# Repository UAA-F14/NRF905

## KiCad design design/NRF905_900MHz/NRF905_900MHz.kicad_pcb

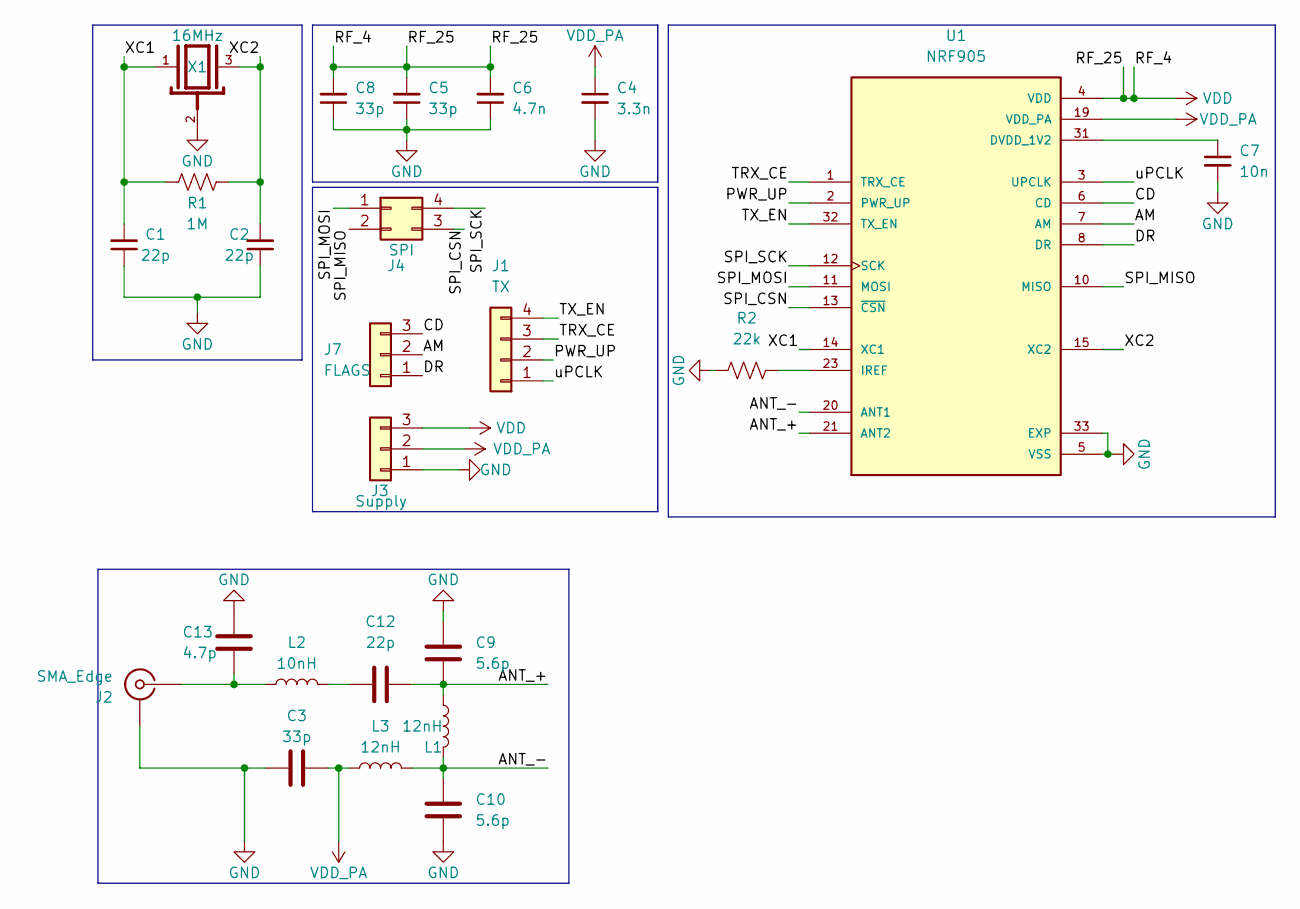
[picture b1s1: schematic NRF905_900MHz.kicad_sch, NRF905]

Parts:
C1, C2, C12: 22p; C_0603_1608Metric
C3, C5, C8: 33p; C_0603_1608Metric
C4: 3.3n; C_0603_1608Metric
C6: 4.7n; C_0603_1608Metric
C7: 10n; C_0603_1608Metric
C9, C10: 5.6p; C_0603_1608Metric
C13: 4.7p; C_0603_1608Metric
J1: TX; PinSocket_1x04_P2.54mm_Vertical
J2: SMA_Edge; SMA_Amphenol_132291-12_Vertical
J3: Supply; PinHeader_1x03_P2.54mm_Vertical
J4: SPI
J7: FLAGS; PinHeader_1x03_P2.54mm_Vertical
L1, L3: 12nH; L_0603_1608Metric
L2: 10nH; L_0603_1608Metric
R1: 1M; R_0603_1608Metric
R2: 22k; R_0603_1608Metric
U1: NRF905; QFN-32-1EP_5x5mm_P0.5mm_EP3.1x3.1mm; MPN NRF905
X1: 16MHz; XTAL_ABM3B-16.000MHZ-10-1-U-T; MPN X322516MLB4SI

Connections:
/AM: J7.2, U1.7 (AM)
/ANT_+: C9.2, C12.2, L1.1, U1.21 (ANT2)
/ANT_-: C10.1, L1.2, L3.2, U1.20 (ANT1)
/CD: J7.3, U1.6 (CD)
/DR: J7.1, U1.8 (DR)
/PWR_UP: J1.2, U1.2 (PWR_UP)
/SPI_CSN: J4.3, U1.13 (~CSN); also elsewhere on the board
/SPI_MISO: J4.2, U1.10 (MISO); also elsewhere on the board
/SPI_MOSI: J4.1, U1.11 (MOSI); also elsewhere on the board
/SPI_SCK: J4.4, U1.12 (SCK); also elsewhere on the board
/TRX_CE: J1.3, U1.1 (TRX_CE)
/TX_EN: J1.4, U1.32 (TX_EN)
/XC1: C1.2, R1.2, U1.14 (XC1), X1.1
/XC2: C2.2, R1.1, U1.15 (XC2), X1.3
/uPCLK: J1.1, U1.3 (UPCLK)
GND: C1.1, C2.1, C3.1, C4.2, C5.1, C6.1, C7.2, C8.1, C9.1, C10.2, C13.2, J2.2 (Ext), J3.1, R2.2, U1.5 (VSS), U1.9 (VSS), U1.16 (VSS), U1.18 (VSS), U1.22 (VSS), U1.24 (VSS), U1.26 (VSS), U1.27 (VSS), U1.28 (VSS), U1.29 (VSS), U1.30 (VSS), U1.33 (EXP), X1.2, X1.4
unnamed: C12.1, L2.2
unnamed: C13.1, J2.1 (In), L2.1
unnamed: C7.1, U1.31 (DVDD_1V2)
unnamed: R2.1, U1.23 (IREF)
VDD: C5.2, C6.2, C8.2, J3.3, U1.4 (VDD), U1.17 (VDD), U1.25 (VDD)
VDD_PA: C3.2, C4.1, J3.2, L3.1, U1.19 (VDD_PA)

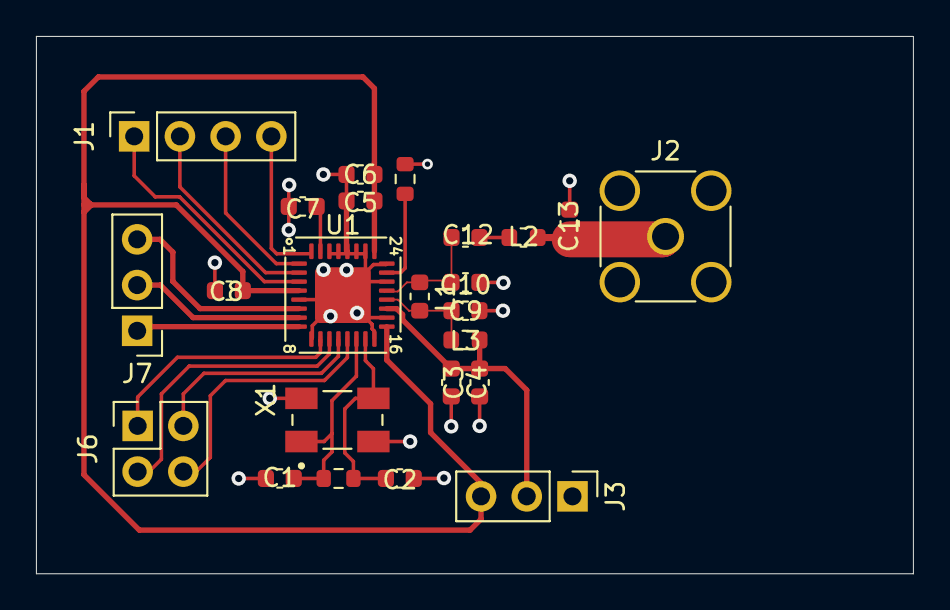
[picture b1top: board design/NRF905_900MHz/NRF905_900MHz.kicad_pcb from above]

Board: 2 copper layers, 48.7 x 29.9 mm, 24 parts (0 on the bottom side), 22 nets.

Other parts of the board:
J6: SPI; PinSocket_2x02_P2.54mm_Vertical

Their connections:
/SPI_CSN: J6.4; also elsewhere on the board
/SPI_MISO: J6.1; also elsewhere on the board
/SPI_MOSI: J6.2; also elsewhere on the board
/SPI_SCK: J6.3; also elsewhere on the board

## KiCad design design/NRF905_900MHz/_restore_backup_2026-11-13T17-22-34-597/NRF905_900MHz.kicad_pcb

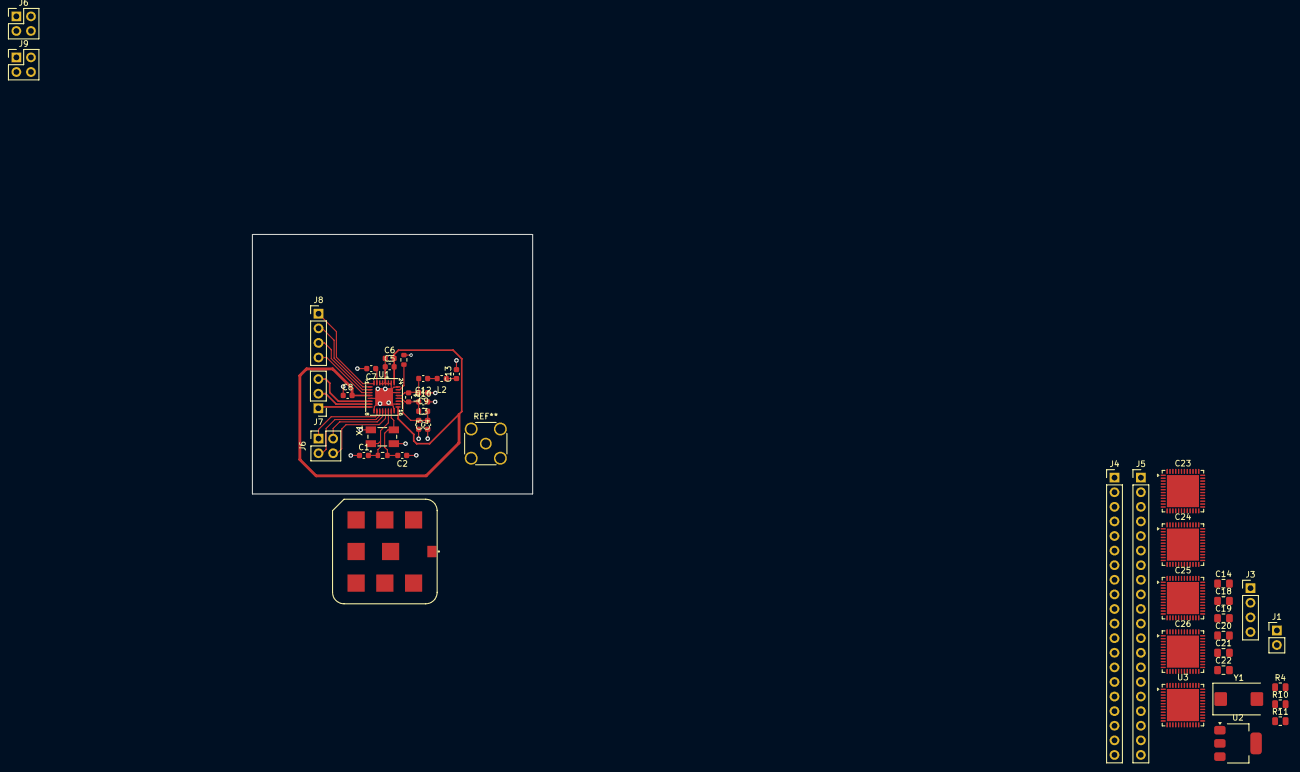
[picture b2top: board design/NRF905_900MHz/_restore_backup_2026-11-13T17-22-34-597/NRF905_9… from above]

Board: 2 copper layers, 48.8 x 45.2 mm, 45 parts (0 on the bottom side), 61 nets.

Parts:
AE1: 50 Ohm; GNSS_Ceramic_Antenna_18.0x18.0mm
C1, C2, C12: 22p; C_0603_1608Metric
C3, C5, C8: 33p; C_0603_1608Metric
C4: 3.3n; C_0603_1608Metric
C6: 4.7n; C_0603_1608Metric
C7: 10n; C_0603_1608Metric
C9, C10: 5.6p; C_0603_1608Metric
C13: 4.7p; C_0603_1608Metric
C14: 4.7uF; C_0805_2012Metric_Pad1.18x1.45mm_HandSolder
C18: 100nF; C_0805_2012Metric_Pad1.18x1.45mm_HandSolder
C19, C20: 22pF; C_0805_2012Metric_Pad1.18x1.45mm_HandSolder
C21: 10uF; C_0805_2012Metric_Pad1.18x1.45mm_HandSolder
C22: 22uF; C_0805_2012Metric_Pad1.18x1.45mm_HandSolder
C23: 1uF; QFN-48-1EP_7x7mm_P0.5mm_EP5.6x5.6mm
C24, C25, C26: 100nF; QFN-48-1EP_7x7mm_P0.5mm_EP5.6x5.6mm
J1: V_Battery; PinHeader_1x02_P2.54mm_Vertical
J3: STLINK; PinHeader_1x04_P2.54mm_Vertical
J4: BlackPill; PinHeader_1x20_P2.54mm_Vertical
J5: Conn_01x20_Socket; PinHeader_1x20_P2.54mm_Vertical
J6: SPI; PinSocket_2x02_P2.54mm_Vertical
J6#2: SPI; PinHeader_2x02_P2.54mm_Vertical
J7: FLAGS; PinHeader_1x03_P2.54mm_Vertical
J8: SPI; PinHeader_1x04_P2.54mm_Vertical
J9: TX; PinHeader_2x02_P2.54mm_Vertical
L1, L3: 12nH; L_0603_1608Metric
L2: 10nH; L_0603_1608Metric
R1: 1M; R_0603_1608Metric
R2: 22k; R_0603_1608Metric
R4, R10, R11: 10k; R_0805_2012Metric
U1: NRF905; QFN-32-1EP_5x5mm_P0.5mm_EP3.1x3.1mm
U2: AMS1117-3.3; SOT-223-3_TabPin2
U3: STM32F411CEUx; QFN-48-1EP_7x7mm_P0.5mm_EP5.6x5.6mm
X1: 16MHz; XTAL_ABM3B-16.000MHZ-10-1-U-T
Y1: 8MHz; Crystal_SMD_EuroQuartz_MQ2-2Pin_7.0x5.0mm

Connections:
3.3V: J4.18, J5.20
5V: J4.20, J5.18
/AM: J7.2, U1.7 (AM)
/ANT_+: C9.2, C12.2, L1.1, U1.21 (ANT2)
/ANT_-: C10.1, L1.2, L3.2, U1.20 (ANT1)
/CD: J7.3, U1.6 (CD)
/DR: J7.1, U1.8 (DR)
/PWR_UP: J8.3, U1.2 (PWR_UP)
/SPI_CSN: J6.4, U1.13 (~CSN)
/SPI_MISO: J6.1, U1.10 (MISO)
/SPI_MOSI: J6.2, U1.11 (MOSI)
/SPI_SCK: J6.3, U1.12 (SCK)
/TRX_CE: J8.2, U1.1 (TRX_CE)
/TX_EN: J8.1, U1.32 (TX_EN)
/XC1: C1.2, R1.2, U1.14 (XC1), X1.1
/XC2: C2.2, R1.1, U1.15 (XC2), X1.3
/uPCLK: J8.4, U1.3 (UPCLK)
A0: J4.6, U3.10 (PA0)
A1: J4.7, U3.11 (PA1)
A2: J4.8, U3.12 (PA2)
A3: J4.9, U3.13 (PA3)
A4: J4.10, U3.14 (PA4)
A5: J4.11, U3.15 (PA5)
A6: J4.12, U3.16 (PA6)
A7: J4.13, U3.17 (PA7)
A8: J5.5, U3.29 (PA8)
A9: J5.6, U3.30 (PA9)
A10: J5.7, U3.31 (PA10)
A11: J5.8, U3.32 (PA11)
A12: J5.9, U3.33 (PA12)
A15: J5.10, U3.38 (PA15)
B0: J4.14, U3.18 (PB0)
B1: J4.15, U3.19 (PB1)
B3: J5.11, U3.39 (PB3)
B4: J5.12, U3.40 (PB4)
B5: J5.13, U3.41 (PB5)
B6: J5.14, U3.42 (PB6)
B7: J5.15, U3.43 (PB7)
B8: J5.16, U3.45 (PB8)
B10: J4.17, U3.21 (PB10)
B12: J5.1, U3.25 (PB12)
B13: J5.2, U3.26 (PB13)
B14: J5.3, U3.27 (PB14)
B15: J5.4, U3.28 (PB15)
BOOT0: R10.1, U3.44 (BOOT0)
BOOT1: R11.1, U3.20 (PB2)
GND: C1.1, C2.1, C3.1, C4.2, C5.1, C6.1, C7.2, C8.1, C9.1, C10.2, C13.2, C14.2, C18.1, C19.2, C20.2, C21.2, C22.2, C23.2, C24.2, C25.2, C26.2, J1.1, J3.4, J4.19, J5.17, J5.19, R2.2, U1.5 (VSS), U1.9 (VSS), U1.16 (VSS), U1.18 (VSS), U1.22 (VSS), U1.24 (VSS), U1.26 (VSS), U1.27 (VSS), U1.28 (VSS), U1.29 (VSS), U1.30 (VSS), U1.33 (EXP), U2.1 (GND), U3.8 (VSSA), U3.23 (VSS), U3.35 (VSS), U3.47 (VSS), U3.49 (VSS), X1.2, X1.4
NRST: C18.2, R4.1, U3.7 (NRST)
unnamed: AE1.1 (A_1), C13.1, L2.1
unnamed: C12.1, L2.2
unnamed: C7.1, U1.31 (DVDD_1V2)
unnamed: R2.1, U1.23 (IREF)
unnamed: C14.1, U3.22 (VCAP1)
OSC_IN: C19.1, U3.5 (PH0), Y1.2
OSC_OUT: C20.1, U3.6 (PH1), Y1.1
SWCLK: J3.3, U3.37 (PA14)
SWDIO: J3.2, U3.34 (PA13)
VCC: C22.1, C23.1, C24.1, C25.1, C26.1, J3.1, R4.2, U2.2 (VO), U3.1 (VBAT), U3.9 (VDDA), U3.24 (VDD), U3.36 (VDD), U3.48 (VDD)
VDD: C5.2, C6.2, C8.2, U1.4 (VDD), U1.17 (VDD), U1.25 (VDD)
VDD_PA: C3.2, C4.1, L3.1, U1.19 (VDD_PA)
VIN: C21.1, J1.2, U2.3 (VI)

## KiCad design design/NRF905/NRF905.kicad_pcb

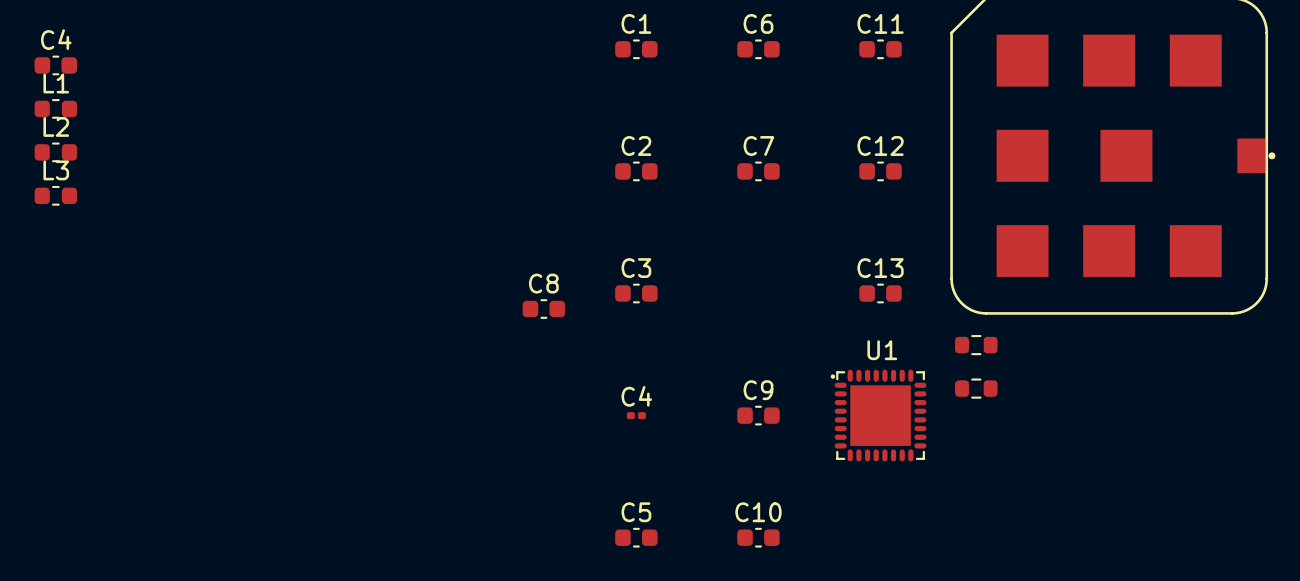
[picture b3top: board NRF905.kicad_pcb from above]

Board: 2 copper layers, 21 parts (0 on the bottom side), 11 nets, no tracks yet.

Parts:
AE1: 50 Ohm; GNSS_Ceramic_Antenna_18.0x18.0mm
C1, C2: 22p; C_0603_1608Metric
C3, C9, C10, C11, C12, C13: C; C_0603_1608Metric
C4: 3.3n; C_0201_0603Metric
C4#2: 3.3n; C_0603_1608Metric
C5, C8: 33p; C_0603_1608Metric
C6: 4.7n; C_0603_1608Metric
C7: 10n; C_0603_1608Metric
L1, L2, L3: L; L_0603_1608Metric
R1: 1M; R_0603_1608Metric
R2: 22k; R_0603_1608Metric
U1: NRF905; QFN50P500X500X90-33N

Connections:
/XC1: C1.2, R1.2, U1.14 (XC1)
/XC2: C2.2, R1.1, U1.15 (XC2)
GND: C1.1, C2.1, C3.1, C4.1, C4#2.2, C5.1, C6.1, C7.2, C8.1, C9.1, C10.2, C13.2, R2.2, U1.5 (VSS), U1.9 (VSS), U1.16 (VSS), U1.18 (VSS), U1.22 (VSS), U1.24 (VSS), U1.26 (VSS), U1.27 (VSS), U1.28 (VSS), U1.29 (VSS), U1.30 (VSS)
unnamed: AE1.1 (A_1), C12.1, C13.1
unnamed: C12.2, L3.1
unnamed: C9.2, C11.1, L2.2, L3.2, U1.20 (ANT1)
unnamed: C10.1, C11.2, L1.2, L2.1, U1.21 (ANT2)
unnamed: C7.1, U1.31 (DVDD_1V2)
unnamed: R2.1, U1.23 (IREF)
VDD: C5.2, C6.2, C8.2, U1.4 (VDD), U1.17 (VDD), U1.25 (VDD)
VDD_PA: C3.2, C4.2, C4#2.1, L1.1, U1.19 (VDD_PA)
